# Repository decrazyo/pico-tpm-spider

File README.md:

# Pico TPM SPIder

Pico TPM SPIder is a Volume Master Key (VMK) recovery tool for SPI-based TPM 2.0 chips, built on [Raspberry Pi Pico](https://www.digikey.com/en/products/detail/raspberry-pi/SC0915/13624793) hardware.
It passively monitors SPI communication with a discrete TPM 2.0 chip and parses transactions in real time to extract the VMK.
This project specifically targets the STMicroelectronics [ST33TPHF2XSPI](https://www.st.com/en/product/st33tphf2xspi) used in several Dell laptops,
though other devices and TPM 2.0 chips may be compatible.

Pico TPM SPIder is designed to capture TPM SPI traffic clocked at 10MHz to 50MHz with or without the use of a chip select signal.
Lower frequencies can be supported by modifying [sniffer.pio](https://github.com/decrazyo/pico-tpm-spider/blob/main/sniffer.pio).
Higher frequencies may be supported through overclocking.

[Watch the video!](https://www.youtube.com/watch?v=U-wuOeI9vQg)

Two protection modes are supported:
 + TPM only, where the PC can boot without user intervention
 + TPM + PIN, where bitlocker asks for a PIN code on boot. In this mode the PIN must be known in order to sniff the TPM blob

See Build section for instruction on how to choose between the two modes.

## Compatibility

The following devices have been tested.

| device               | working | bus voltage | chip select  | notes |
|----------------------|---------|-------------|--------------|-------|
| Dell Latitude 5320   | yes     | 3.3V        | inaccessible | SPI flash memory, unpopulated SPI connector |
| Dell Latitude 5430   | yes     | ?           | ?            | Tested by [volttest-jpg](https://github.com/volttest-jpg) |
| Dell Latitude 5431   | yes     | 3.3V        | inaccessible | SPI flash memory |
| Dell Precision 3490  | yes     | 1.8V        | inaccessible | SPI flash memory |
| HP EliteBook 645 G10 | yes     | 3.3V        | inaccessible | SPI flash memory, use a shorter sniffer timeout (~30ns) |
| HP Elitebook 840 G10 | yes     | ?           | ?            | Tested by [volttest-jpg](https://github.com/volttest-jpg) |

> [!CAUTION]
> Check the voltage of your target device's SPI bus!
> The Raspberry Pi Pico is only designed to work with 3.3V logic.
> A converter should be used to interface with other bus voltages.
> The [TXS0108E](https://www.amazon.com/TXS0108E-Bi-Directional-Converter-Channel-Conversion/dp/B0F285G5JT) has been proven to work for this.

## Hardware

The following methods of connecting to the SPI bus have been tested.

### WSON8 Probe

All of the tested devices have a [SPI flash memory chip](https://www.winbond.com/resource-files/W25R256JV%20RevD%2006162020.pdf), presumably the BIOS/UEFI, on the same bus as the TPM chip.
A [WSON8 probe](https://www.amazon.com/Amagogo-Download-Efficient-Industrial-Electronic/dp/B0DRZGRN81) can be used to connect to the SPI bus via the flash chip.
This is by far the easiest way to connect to the SPI bus.

### Custom PCB

A custom PCB, inspired by [stacksmashing's design](https://github.com/stacksmashing/pico-tpmsniffer), is provided in the `hardware` directory and simplifies connecting to the SPI bus on Dell Latitude 5320 laptops via an unpopulated connector.
The PCB provides two methods for interfacing with the connector.

1) **Pogo Pins** (hard to solder, easy to use)  
The board includes footprints for pogo pins that align with the Latitude 5320's unpopulated connector.

2) **Flat Flex Ribbon** (easy to solder, hard to use)  
The board accommodates a flat flex ribbon connector.
A flat flex ribbon can be connected to the PCB and then pressed against the Latitude 5320's unpopulated connector.

Since the unpopulated connector does not include a chip select (CS) signal, the PCB grounds the Pi Pico's CS input (GPIO 3) by default.
Cutting jumper `JP1` will disconnect the CS input from GND.  

| description                | part number |
|----------------------------|-------------|
| Pogo Pins                  | [P50-B1-16mm](https://www.amazon.com/KooingTech-Pressure-Testing-Fingers-Printed/dp/B0DMGG23QF) |
| Flat Flex Ribbon           | [0982660209](https://www.digikey.com/en/products/detail/molex/0982660209/2750458) |
| Flat Flex Ribbon Connector | [CF31201D0R0-05-NH](https://www.digikey.com/en/products/detail/cvilux-usa/CF31201D0R0-05-NH/15792943) |

### Needle Probes / Soldering

[Needle probes](https://sensepeek.com/4x-sq10-probes-with-test-wires) can be used to connect to any exposed part of the SPI bus.
Such a setup can be precarious so soldering may be a better option if you have some [30 gauge wire](https://www.amazon.com/Jonard-R-30B-0050-Replacement-Kynar-Dispenser/dp/B006C4ABR0) and a steady hand.

> [!NOTE]
> Interference can cause various issues including
> failure to boot, entering Dell's "manufacturing mode", BIOS/UEFI corruption, and failure to recover the VMK.
> Keep your SPI wires short, away from sources of interference, and preferably shielded to avoid those issues.

## Build

Download the [Raspberry Pi Pico SDK](https://github.com/raspberrypi/pico-sdk).  
Install dependencies specified by the Raspberry Pi Pico SDK documentation.  
Build the project.  

```
git clone https://github.com/decrazyo/pico-tpm-spider.git
cd pico-tpm-spider
export PICO_SDK_PATH=/path/to/your/Pico-SDK
mkdir build
cd build
cmake ..
make
```

The firmware works in either TPM or TPM+PIN mode; by default the build produces a TPM only firmware. To build a TPM+PIN firmware, change line 13 in  `main.c` from `#undef TPM_AND_PIN` to `#define TPM_AND_PIN`

> [!NOTE]
> Built on Debian 12.

## Install

Press and hold the `BOOTSEL` button while plugging in the Pi Pico to make it appear as a mass storage device.  
Install the Pico TPM SPIder firmware by copying `pico-tpm-spider/build/pico-tpm-spider.uf2` to the Pi Pico's mass storage device.  

## Usage

Connect the Pi Pico's pins to your TPM chip according to the following table.  

| pico pin | spi signal |
|----------|------------|
| GPIO 0   | MOSI       |
| GPIO 1   | MISO       |
| GND      | GND        |
| GPIO 2   | CLK        |
| GPIO 3   | CS or GND  |

> [!NOTE]
> The use of a chip select (CS) signal is optional but recommenced since it significantly reduces the amount of data that the Pi Pico needs to parse.

> [!IMPORTANT]
> If you're not providing the Pi Pico with the TPM's CS signal then GPIO 3 must be grounded!
> GPIO 3 is grounded by default on the provided PCB.  

Connect to the Pi Pico with your serial terminal of choice and boot the target system.  

```
picocom -q /dev/ttyACM0 -b 115200
```

### with TPM only
You should see output similar to this.

> Capturing SPI traffic into 12 16384-byte buffers.  
> Expecting TPM only protection. VMK will be output if found.
> Press any key to finalize the capture and reboot.  
> VMK: DEADC0DEDEADC0DEDEADC0DEDEADC0DEDEADC0DEDEADC0DEDEADC0DEDEADC0DE  

> [!NOTE]
> If the VMK does not automatically appear by the time the system has booted then press a key to finalize the capture.
> This will cause the Pi Pico to parse any data remaining in its buffer and may recover the VMK.  

The recovered VMK can be used with the `dislocker` utility to decrypt the target system's hard drive.  

```
echo DEADC0DEDEADC0DEDEADC0DEDEADC0DEDEADC0DEDEADC0DEDEADC0DEDEADC0DE | xxd -r -p > vmk.bin
mkdir /mnt/dislocker
mkdir /mnt/drive_c
dislocker -K vmk.bin /dev/sdb3 /mnt/dislocker
mount -t ntfs-3g -o remove_hiberfile,recover /mnt/dislocker/dislocker-file /mnt/drive_c
ls /mnt/drive_c/
```

### with TPM+PIN
a PKEY will be output after entering the PIN to the target computer:

> Capturing SPI traffic into 12 16384-byte buffers.  
> Expecting TPM and PIN protection. Pkey will be output if found.  
> Press any key to finalize the capture and reboot.  
> PKEY: 80216F353D57DD01540000006F3E05FA067913FCB8714AC58FCD94E3E25E4D2E20F906C8CF40F1B9F59199B538A953E168A71D3D7B5C07331DF4B931FC3043565B90DC98E9F7225C  

You will need [SPITkey](https://github.com/en4rab/SPITkey) and the output of a first dislocker run to obtain the FVEK:

```
dislocker -vvvv /dev/sda3 >dislocker.log
echo 80216F353D57DD01540000006F3E05FA067913FCB8714AC58FCD94E3E25E4D2E20F906C8CF40F1B9F59199B538A953E168A71D3D7B5C07331DF4B931FC3043565B90DC98E9F7225C >tpm-blob
python SPITKEY.py -l dislocker.log -p <bitlocker PIN> -t tpm-blob
```

SPITKEY will produce a file named `<machinename>.fvek`, use it with dislocker:

```
dislocker -V /dev/sda3 -k <machinename>.fvek /mnt/dislocker
mount -t ntfs-3g -o remove_hiberfile,recover /mnt/dislocker/dislocker-file /mnt/drive_c
ls /mnt/drive_c/
```

## Related Projects
* https://github.com/decrazyo/spi-analyzer
* https://github.com/ReversecLabs/bitlocker-spi-toolkit
* https://github.com/NoobieDog/TPM-Sniffing
* https://github.com/stacksmashing/pico-tpmsniffer
* https://github.com/zaphoxx/pico-tpmsniffer-spi
* https://github.com/aplhk/pico-spisniffer
* https://github.com/jerji/picobitlkr
* https://github.com/en4rab/SPITkey

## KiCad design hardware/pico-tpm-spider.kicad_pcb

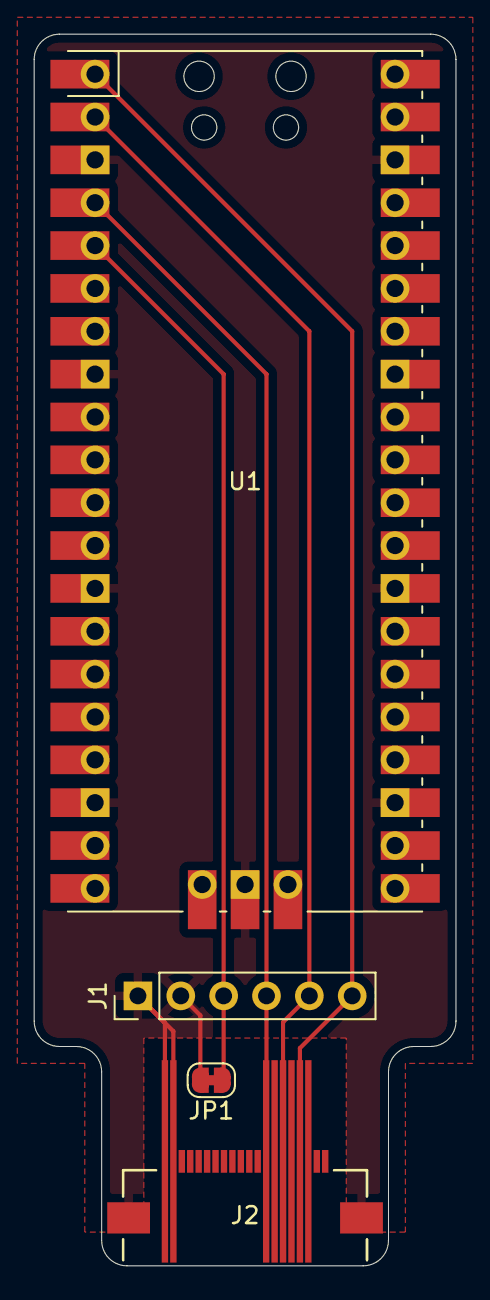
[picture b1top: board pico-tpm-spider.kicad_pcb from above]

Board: 2 copper layers, 25.0 x 73.0 mm, 4 parts (0 on the bottom side), 5 nets.

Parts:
J1: Conn_01x06; PinHeader_1x06_P2.54mm_Vertical
J2: CF31201D0R0-05-NH; CONN_CF31201D0R0-05-NH_CVI
JP1: GND CS; SolderJumper-2_P1.3mm_Bridged_RoundedPad1.0x1.5mm
U1: Pico; RPi_Pico_SMD_TH

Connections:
/CLK: J1.4, J2.13, U1.4 (GPIO2)
/CS: J1.3, JP1.1 (A), U1.5 (GPIO3)
/MISO: J1.5, J2.15, U1.2 (GPIO1)
/MOSI: J1.6, J2.17, U1.1 (GPIO0)
GND: J1.1, J1.2, J2.1, J2.2, J2.21, J2.22, JP1.2 (B), U1.3 (GND), U1.8 (GND), U1.13 (GND), U1.18 (GND), U1.23 (GND), U1.28 (GND), U1.38 (GND), U1.42 (GND)

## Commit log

2026-02-11 improve performance, parsing, and docs
2026-03-06 improve sniffing, parsing, and docs
2026-04-05 add cyphercon slides
